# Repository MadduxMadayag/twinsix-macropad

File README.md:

# TwinSix — Custom 12-Key Macropad

A custom 12-key mechanical macropad built around a designed PCB, an RP2040-based controller, QMK firmware, and a 3D-printed enclosure. The two 2×3 key clusters leave an open center section for the controller and create a compact, symmetrical layout.

## Overview

TwinSix is a hardware design project covering PCB layout, keyboard firmware configuration, mechanical modeling, and final assembly. The board uses a 2×6 key matrix and a centrally mounted RP2040-based controller connected over USB-C.

**Project highlights**
- Designed a custom PCB and switch layout in KiCad for 12 mechanical keys.
- Routed the switch matrix and integrated a centrally positioned controller footprint.
- Configured QMK firmware, including default key mappings and Vial-related configuration files.
- Modeled a fitted enclosure and switch openings for 3D printing.
- Assembled the PCB, mechanical switches, keycaps, and enclosure into a finished device.

## Finished build

| Top | Underside |
| --- | --- |
|  |  |

## PCB design

The PCB arranges twelve switch footprints in two groups of six, with the controller located between them. The firmware defines **2 rows and 6 columns** using RP2040 GPIO pins.

| PCB routing | 3D PCB preview |
| --- | --- |
|  |  |

The editable schematic, board layout, and project configuration are in [`hardware/kicad/`](hardware/kicad/). Fabrication outputs are in [`hardware/fabrication/`](hardware/fabrication/).

## Mechanical design

The enclosure was modeled around the PCB and switch geometry, with a recessed top opening and a USB-C access cutout. Printable STL files and a DXF drawing are included in [`mechanical/`](mechanical/).

| Enclosure CAD | Switch assembly CAD |
| --- | --- |
|  |  |

## Firmware

The project uses **QMK** on an **RP2040** controller. The firmware source in [`firmware/`](firmware/) includes matrix pin assignments, default keymap, and Vial configuration. Prebuilt UF2 firmware images from the project archive are included under [`firmware/prebuilt/`](firmware/prebuilt/).

The supplied default keymap is:

```text
Left cluster        Right cluster
  1  2  3              4  5  6
  7  8  9              0  A  B
```

For development, place the firmware files into the appropriate `keyboards/handwired/twinsix/` directory in a QMK firmware checkout. The original project documents the build command:

```bash
qmk compile -kb handwired/twinsix -km default
```

**Note:** The included firmware files are an archived project configuration, not a standalone QMK checkout. Review the board revision and firmware before flashing any UF2 image.

## Repository layout

```text
images/                Project photos and design renders
hardware/kicad/        Editable schematic and PCB design
hardware/fabrication/  PCB fabrication outputs
mechanical/            Enclosure STLs and DXF
firmware/              QMK configuration, keymaps, and UF2 files
```

## Tools and technologies

KiCad · RP2040 · QMK · Vial configuration · 3D CAD · 3D printing · Mechanical keyboard switches

## Project status

A physical prototype has been assembled. This repository preserves the hardware, mechanical, and firmware design artifacts from the build.

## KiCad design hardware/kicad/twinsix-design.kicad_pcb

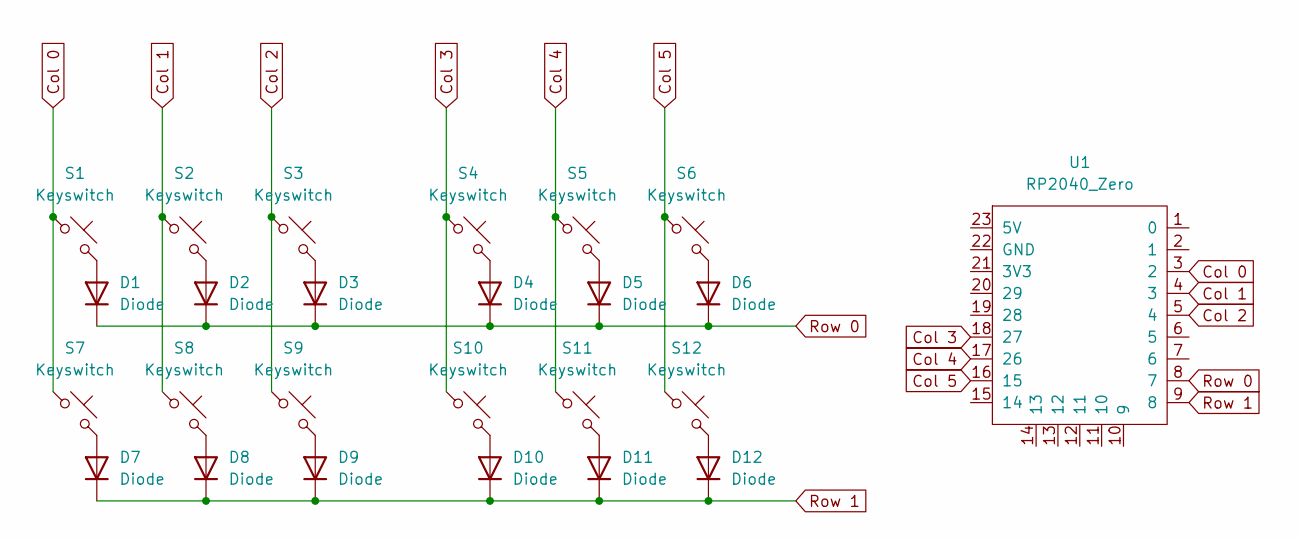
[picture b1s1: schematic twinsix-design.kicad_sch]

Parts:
D1, D2, D3, D4, D5, D6, D7, D8, D9, D10, D11, D12: Diode; Diode_DO-35
S1, S2, S3, S4, S5, S6, S7, S8, S9, S10, S11, S12: Keyswitch; MX_PCB_1.00u
U1: RP2040_Zero

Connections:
Col 0: S1.1, S7.1, U1.3 (2)
Col 1: S2.1, S8.1, U1.4 (3)
Col 2: S3.1, S9.1, U1.5 (4)
Col 3: S4.1, S10.1, U1.18 (27)
Col 4: S5.1, S11.1, U1.17 (26)
Col 5: S6.1, S12.1, U1.16 (15)
unnamed: D1.2 (A), S1.2
unnamed: D2.2 (A), S2.2
unnamed: D3.2 (A), S3.2
unnamed: D4.2 (A), S4.2
unnamed: D5.2 (A), S5.2
unnamed: D6.2 (A), S6.2
unnamed: D7.2 (A), S7.2
unnamed: D8.2 (A), S8.2
unnamed: D9.2 (A), S9.2
unnamed: D10.2 (A), S10.2
unnamed: D11.2 (A), S11.2
unnamed: D12.2 (A), S12.2
Row 0: D1.1 (K), D2.1 (K), D3.1 (K), D4.1 (K), D5.1 (K), D6.1 (K), U1.8 (7)
Row 1: D7.1 (K), D8.1 (K), D9.1 (K), D10.1 (K), D11.1 (K), D12.1 (K), U1.9 (8)

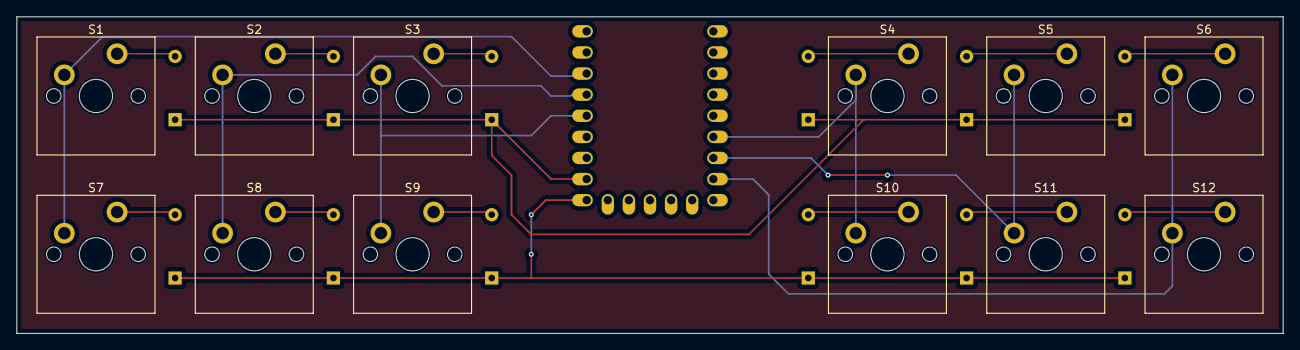
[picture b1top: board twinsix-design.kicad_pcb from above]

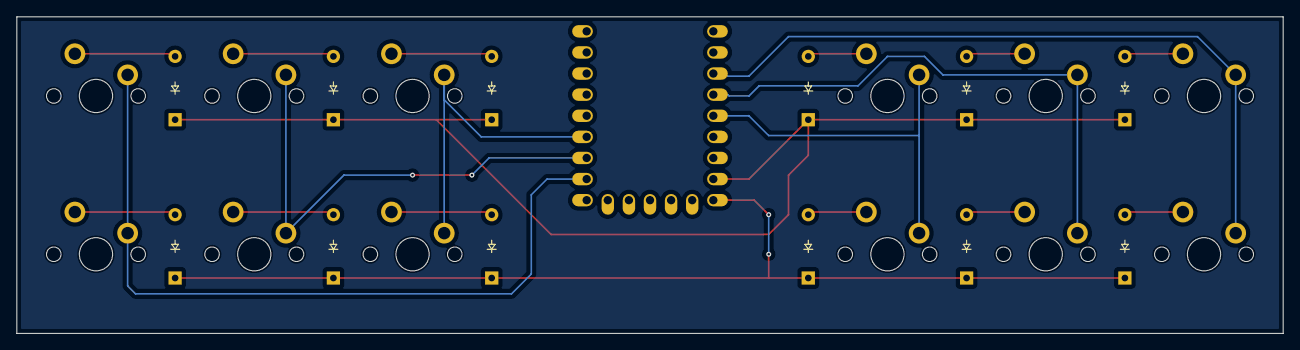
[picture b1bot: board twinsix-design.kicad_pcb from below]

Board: 2 copper layers, 152.4 x 38.1 mm, 25 parts (13 on the bottom side), 20 nets.
